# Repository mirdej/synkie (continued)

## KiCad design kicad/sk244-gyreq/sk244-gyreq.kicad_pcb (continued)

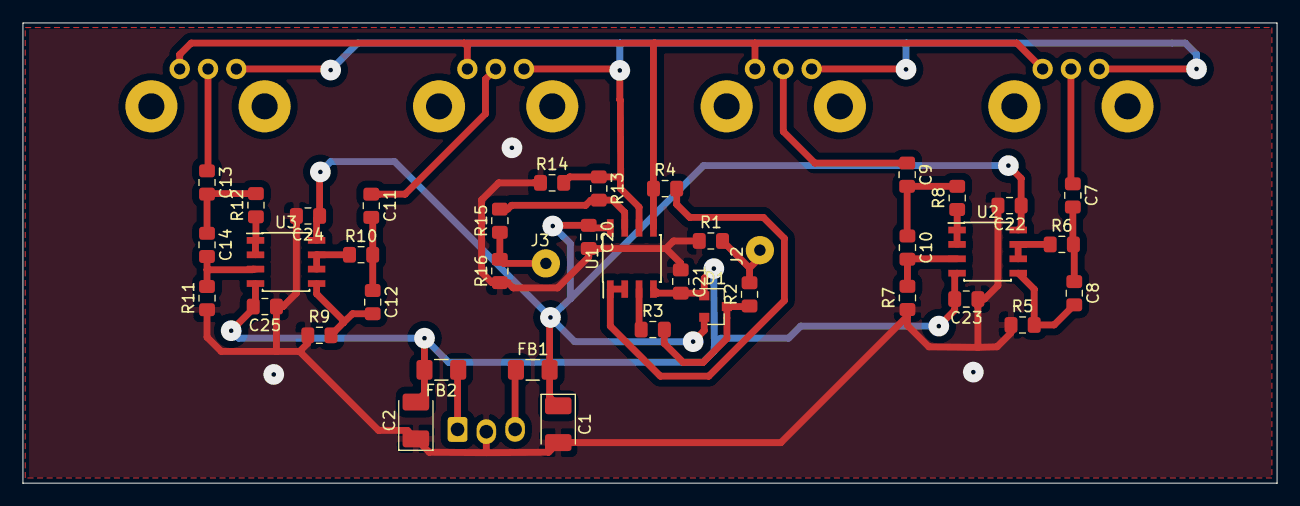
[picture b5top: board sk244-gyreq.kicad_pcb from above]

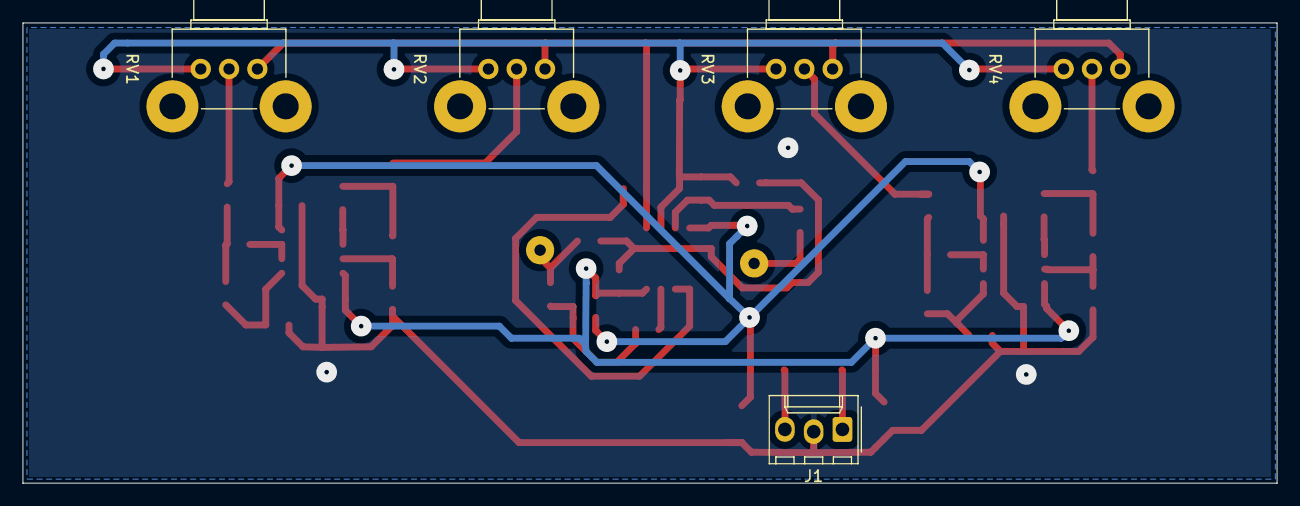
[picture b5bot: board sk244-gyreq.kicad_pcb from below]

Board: 2 copper layers, 110.7 x 40.6 mm, 45 parts (5 on the bottom side), 29 nets.

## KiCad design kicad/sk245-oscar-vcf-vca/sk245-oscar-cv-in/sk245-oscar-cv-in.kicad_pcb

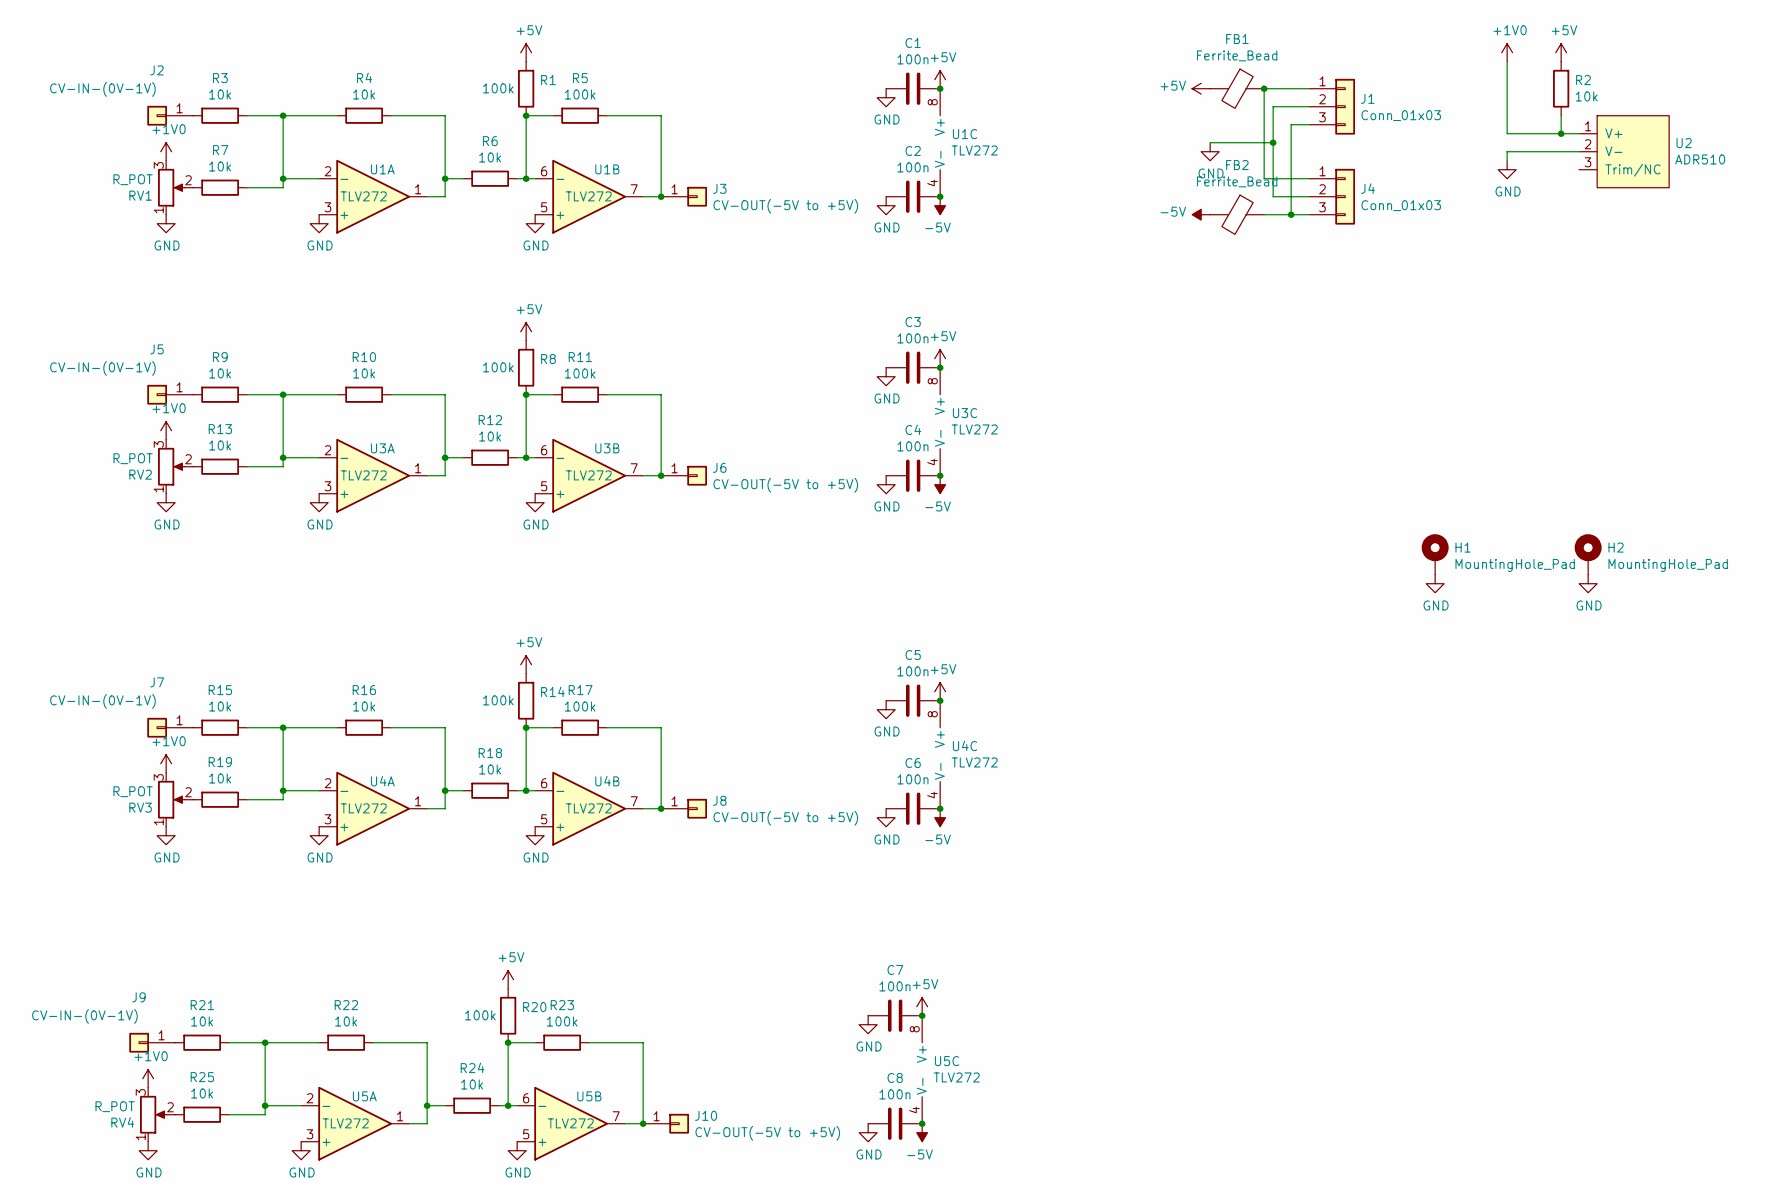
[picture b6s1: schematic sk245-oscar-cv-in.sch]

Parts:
C1, C2, C3, C4, C5, C6, C7, C8: 100n; C_0603_1608Metric_Pad1.05x0.95mm_HandSolder
FB1, FB2: Ferrite_Bead; L_0805_2012Metric_Pad1.15x1.40mm_HandSolder
H1, H2: MountingHole_Pad; MountingHole_3.2mm_M3_Pad
J1, J4: Conn_01x03; Molex_KK-254_AE-6410-03A_1x03_P2.54mm_Vertical
J2, J5, J7, J9: CV-IN-(0V-1V); Solderpad_1mm
J3, J6, J8, J10: CV-OUT(-5V to +5V); Solderpad_1mm
R1, R5, R8, R11, R14, R17, R20, R23: 100k; R_0805_2012Metric_Pad1.15x1.40mm_HandSolder
R2, R3, R4, R6, R7, R9, R10, R12, R13, R15, R16, R18, R19, R21, R22, R24, R25: 10k; R_0805_2012Metric_Pad1.15x1.40mm_HandSolder
RV1, RV2, RV3, RV4: R_POT; Potentiometer_Alps_RK09K_Single_Horizontal
U1, U3, U4, U5: TLV272; SOIC-8_3.9x4.9mm_P1.27mm
U2: ADR510; SOT-23

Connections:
+1V0: R2.1, RV1.3, RV2.3, RV3.3, RV4.3, U2.1 (V+)
+5V: C1.1, C3.1, C5.1, C7.1, FB1.2, R1.2, R2.2, R8.2, R14.2, R20.2, U1.8 (V+), U3.8 (V+), U4.8 (V+), U5.8 (V+)
-5V: C2.1, C4.1, C6.1, C8.1, FB2.2, U1.4 (V-), U3.4 (V-), U4.4 (V-), U5.4 (V-)
GND: C1.2, C2.2, C3.2, C4.2, C5.2, C6.2, C7.2, C8.2, H1.1, H2.1, J1.2, J4.2, RV1.1, RV2.1, RV3.1, RV4.1, U1.3 (+), U1.5 (+), U2.2 (V-), U3.3 (+), U3.5 (+), U4.3 (+), U4.5 (+), U5.3 (+), U5.5 (+)
unnamed: FB1.1, J1.1, J4.1
unnamed: FB2.1, J1.3, J4.3
unnamed: J2.1, R3.2
unnamed: J3.1, R5.1, U1.7
unnamed: J5.1, R9.2
unnamed: J6.1, R11.1, U3.7
unnamed: J7.1, R15.2
unnamed: J8.1, R17.1, U4.7
unnamed: J9.1, R21.2
unnamed: J10.1, R23.1, U5.7
unnamed: R1.1, R5.2, R6.1, U1.6 (-)
unnamed: R3.1, R4.2, R7.1, U1.2 (-)
unnamed: R4.1, R6.2, U1.1
unnamed: R7.2, RV1.2
unnamed: R10.1, R12.2, U3.1
unnamed: R9.1, R10.2, R13.1, U3.2 (-)
unnamed: R8.1, R11.2, R12.1, U3.6 (-)
unnamed: R13.2, RV2.2
unnamed: R14.1, R17.2, R18.1, U4.6 (-)
unnamed: R15.1, R16.2, R19.1, U4.2 (-)
unnamed: R16.1, R18.2, U4.1
unnamed: R19.2, RV3.2
unnamed: R20.1, R23.2, R24.1, U5.6 (-)
unnamed: R21.1, R22.2, R25.1, U5.2 (-)
unnamed: R22.1, R24.2, U5.1
unnamed: R25.2, RV4.2

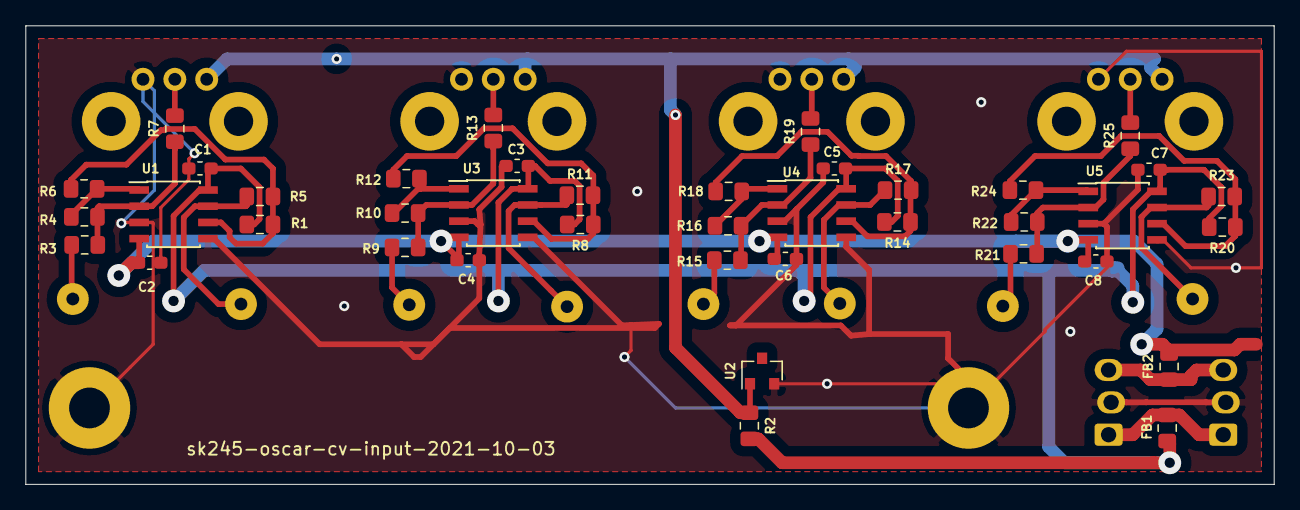
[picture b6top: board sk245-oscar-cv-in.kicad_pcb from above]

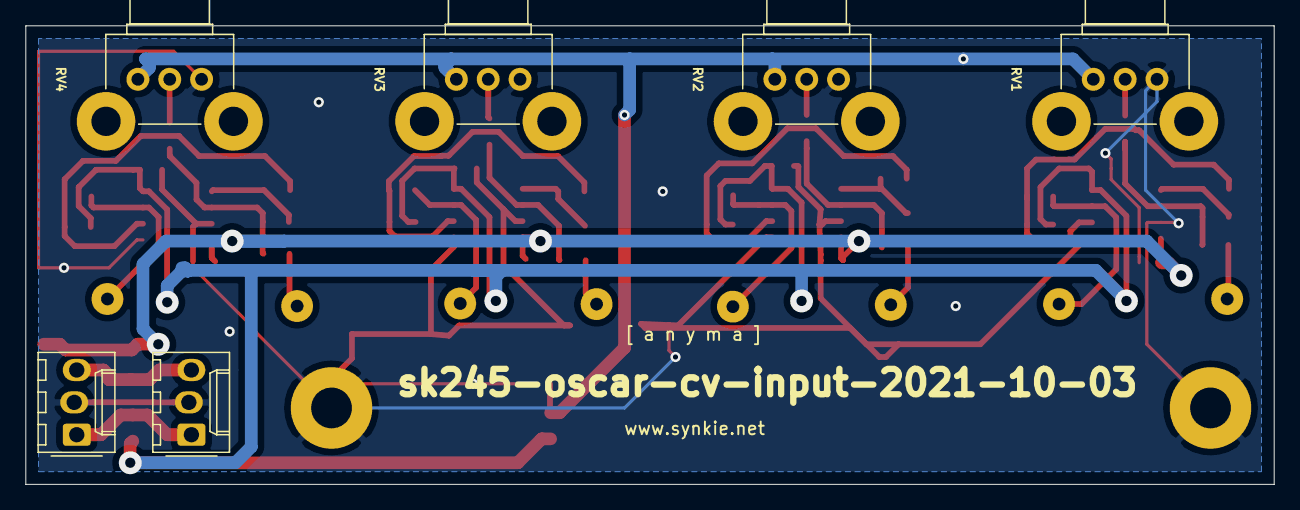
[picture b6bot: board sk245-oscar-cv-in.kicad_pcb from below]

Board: 2 copper layers, 98.0 x 36.0 mm, 56 parts (6 on the bottom side), 30 nets.

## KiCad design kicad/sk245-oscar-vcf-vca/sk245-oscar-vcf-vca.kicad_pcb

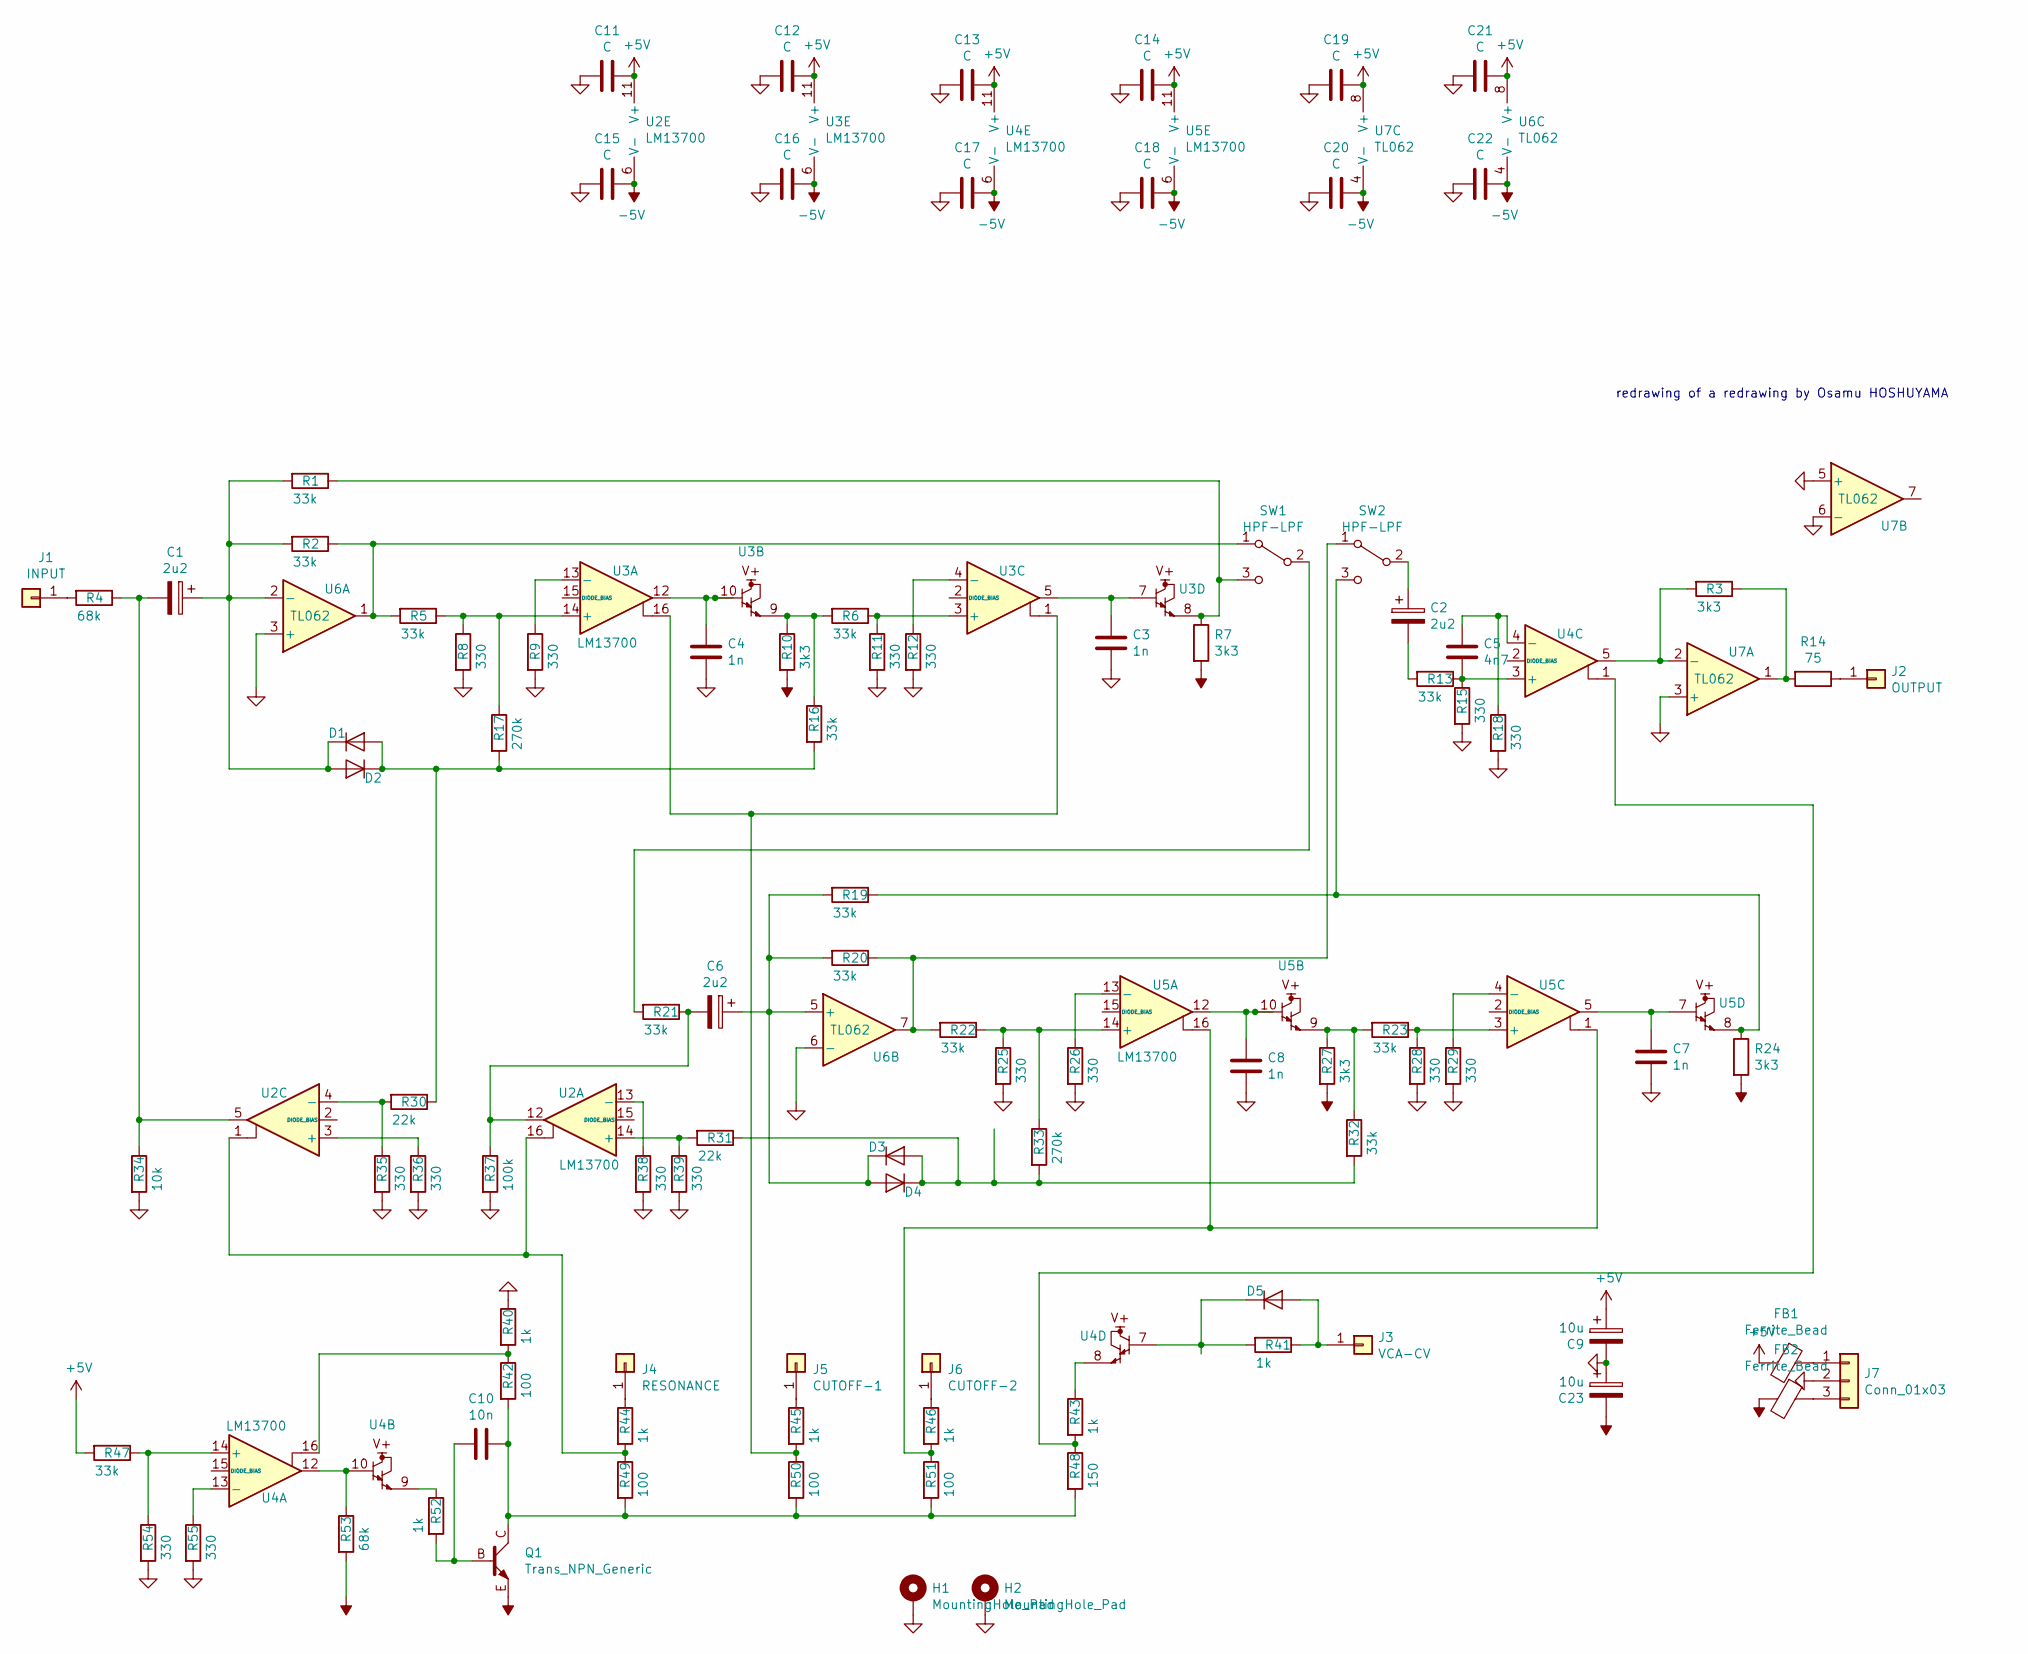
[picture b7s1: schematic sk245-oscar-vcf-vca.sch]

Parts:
C1: 2u2; C_1206_3216Metric_Pad1.42x1.75mm_HandSolder
C2, C6: 2u2; R_1206_3216Metric_Pad1.42x1.75mm_HandSolder
C3, C4, C7, C8: 1n; R_1206_3216Metric_Pad1.42x1.75mm_HandSolder
C5: 4n7; R_1206_3216Metric_Pad1.42x1.75mm_HandSolder
C9, C23: 10u; R_1206_3216Metric_Pad1.42x1.75mm_HandSolder
C10: 10n; C_1206_3216Metric_Pad1.42x1.75mm_HandSolder
C11, C12, C13, C14, C15, C16, C17, C18, C19, C20, C21, C22: C; C_0603_1608Metric_Pad1.05x0.95mm_HandSolder
D1, D2, D3, D4, D5: D; D_MiniMELF_Handsoldering
FB1, FB2: Ferrite_Bead; L_1206_3216Metric_Pad1.42x1.75mm_HandSolder
H1, H2: MountingHole_Pad; MountingHole_3.2mm_M3_ISO7380_Pad
J1: INPUT; Solderpad_1mm
J2: OUTPUT; Solderpad_1mm
J3: VCA-CV; Solderpad_1mm
J4: RESONANCE; Solderpad_1mm
J5: CUTOFF-1; Solderpad_1mm
J6: CUTOFF-2; Solderpad_1mm
J7: Conn_01x03; Molex_KK-254_AE-6410-03A_1x03_P2.54mm_Vertical
Q1: Trans_NPN_Generic; SOT-23_BEC
R1, R2, R5, R6, R13, R16, R19, R20, R21, R22, R23, R32, R47: 33k; R_0805_2012Metric_Pad1.15x1.40mm_HandSolder
R3, R7, R10, R24, R27: 3k3; R_0805_2012Metric_Pad1.15x1.40mm_HandSolder
R4, R53: 68k; R_0805_2012Metric_Pad1.15x1.40mm_HandSolder
R8, R9, R11, R12, R15, R18, R25, R26, R28, R29, R35, R36, R38, R39, R54, R55: 330; R_0805_2012Metric_Pad1.15x1.40mm_HandSolder
R14: 75; R_0805_2012Metric_Pad1.15x1.40mm_HandSolder
R17, R33: 270k; R_0805_2012Metric_Pad1.15x1.40mm_HandSolder
R30, R31: 22k; R_0805_2012Metric_Pad1.15x1.40mm_HandSolder
R34: 10k; R_0805_2012Metric_Pad1.15x1.40mm_HandSolder
R37: 100k; R_0805_2012Metric_Pad1.15x1.40mm_HandSolder
R40, R41, R43, R44, R45, R46, R52: 1k; R_0805_2012Metric_Pad1.15x1.40mm_HandSolder
R42, R49, R50, R51: 100; R_0805_2012Metric_Pad1.15x1.40mm_HandSolder
R48: 150; R_0805_2012Metric_Pad1.15x1.40mm_HandSolder
SW1, SW2: HPF-LPF; PinHeader_1x03_P2.54mm_Vertical
U2, U3, U4, U5: LM13700; SOIC-16_3.9x9.9mm_P1.27mm
U6, U7: TL062; SOIC-8_3.9x4.9mm_P1.27mm

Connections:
+5V: C9.1, C11.1, C12.1, C13.1, C14.1, C19.1, C21.1, FB1.2, R47.2, U2.11 (V+), U3.11 (V+), U4.11 (V+), U5.11 (V+), U6.8 (V+), U7.8 (V+)
-5V: C15.1, C16.1, C17.1, C18.1, C20.1, C22.1, C23.2, FB2.2, Q1.E, R7.2, R10.2, R24.2, R27.2, R53.2, U2.6 (V-), U3.6 (V-), U4.6 (V-), U5.6 (V-), U6.4 (V-), U7.4 (V-)
GND: C3.2, C4.2, C7.2, C8.2, C9.2, C11.2, C12.2, C13.2, C14.2, C15.2, C16.2, C17.2, C18.2, C19.2, C20.2, C21.2, C22.2, C23.1, H1.1, H2.1, J7.2, R8.2, R9.2, R11.2, R12.2, R15.2, R18.2, R25.2, R26.2, R28.2, R29.2, R34.2, R35.2, R36.2, R37.2, R38.2, R39.2, R40.1, R54.2, R55.2, U6.3 (+), U6.6 (-), U7.3 (+), U7.5 (+), U7.6 (-)
unnamed: C1.1, D1.1 (K), D2.2 (A), R1.2, R2.2, U6.2 (-)
unnamed: C1.2, R4.1, R34.1, U2.5
unnamed: C2.1, SW2.2 (B)
unnamed: C2.2, R13.2
unnamed: C3.1, U3.5, U3.7
unnamed: C4.1, U3.10, U3.12
unnamed: C5.1, R18.1, U4.4 (-)
unnamed: C5.2, R13.1, R15.1, U4.3 (+)
unnamed: C6.1, D3.1 (K), D4.2 (A), R19.2, R20.2, U6.5 (+)
unnamed: C6.2, R21.1, R37.1, U2.12
unnamed: C7.1, U5.5, U5.7
unnamed: C8.1, U5.10, U5.12
unnamed: C10.1, Q1.C, R42.2, R48.2, R49.2, R50.2, R51.2
unnamed: C10.2, Q1.B, R52.2
unnamed: D1.2 (A), D2.1 (K), R16.2, R17.2, R30.1
unnamed: D3.2 (A), D4.1 (K), R31.1, R32.2, R33.2
unnamed: D5.1 (K), R41.2, U4.7
unnamed: D5.2 (A), J3.1, R41.1
unnamed: FB1.1, J7.1
unnamed: FB2.1, J7.3
unnamed: J1.1, R4.2
unnamed: J2.1, R14.1
unnamed: J4.1, R44.1
unnamed: J5.1, R45.1
unnamed: J6.1, R46.1
unnamed: R1.1, R7.1, SW1.3 (C), U3.8
unnamed: R2.1, R5.2, SW1.1 (A), U6.1
unnamed: R3.2, U4.5, U7.2 (-)
unnamed: R9.1, U3.13 (-)
unnamed: R6.2, R10.1, R16.1, U3.9
unnamed: R6.1, R11.1, U3.3 (+)
unnamed: R12.1, U3.4 (-)
unnamed: R3.1, R14.2, U7.1
unnamed: R5.1, R8.1, R17.1, U3.14 (+)
unnamed: R19.1, R24.1, SW2.3 (C), U5.8
unnamed: R20.1, R22.2, SW2.1 (A), U6.7
unnamed: R21.2, SW1.2 (B)
unnamed: R22.1, R25.1, R33.1, U5.14 (+)
unnamed: R23.1, R28.1, U5.3 (+)
unnamed: R23.2, R27.1, R32.1, U5.9
unnamed: R26.1, U5.13 (-)
unnamed: R29.1, U5.4 (-)
unnamed: R30.2, R35.1, U2.4 (-)
unnamed: R31.2, R39.1, U2.14 (+)
unnamed: R36.1, U2.3 (+)
unnamed: R38.1, U2.13 (-)
unnamed: R40.2, R42.1, U4.16
unnamed: R43.1, U4.8
unnamed: R43.2, R48.1, U4.1
unnamed: R44.2, R49.1, U2.1, U2.16
unnamed: R45.2, R50.1, U3.1, U3.16
unnamed: R46.2, R51.1, U5.1, U5.16
unnamed: R47.1, R54.1, U4.14 (+)
unnamed: R52.1, U4.9
unnamed: R53.1, U4.10, U4.12
unnamed: R55.1, U4.13 (-)

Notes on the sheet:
redrawing of a redrawing by Osamu HOSHUYAMA

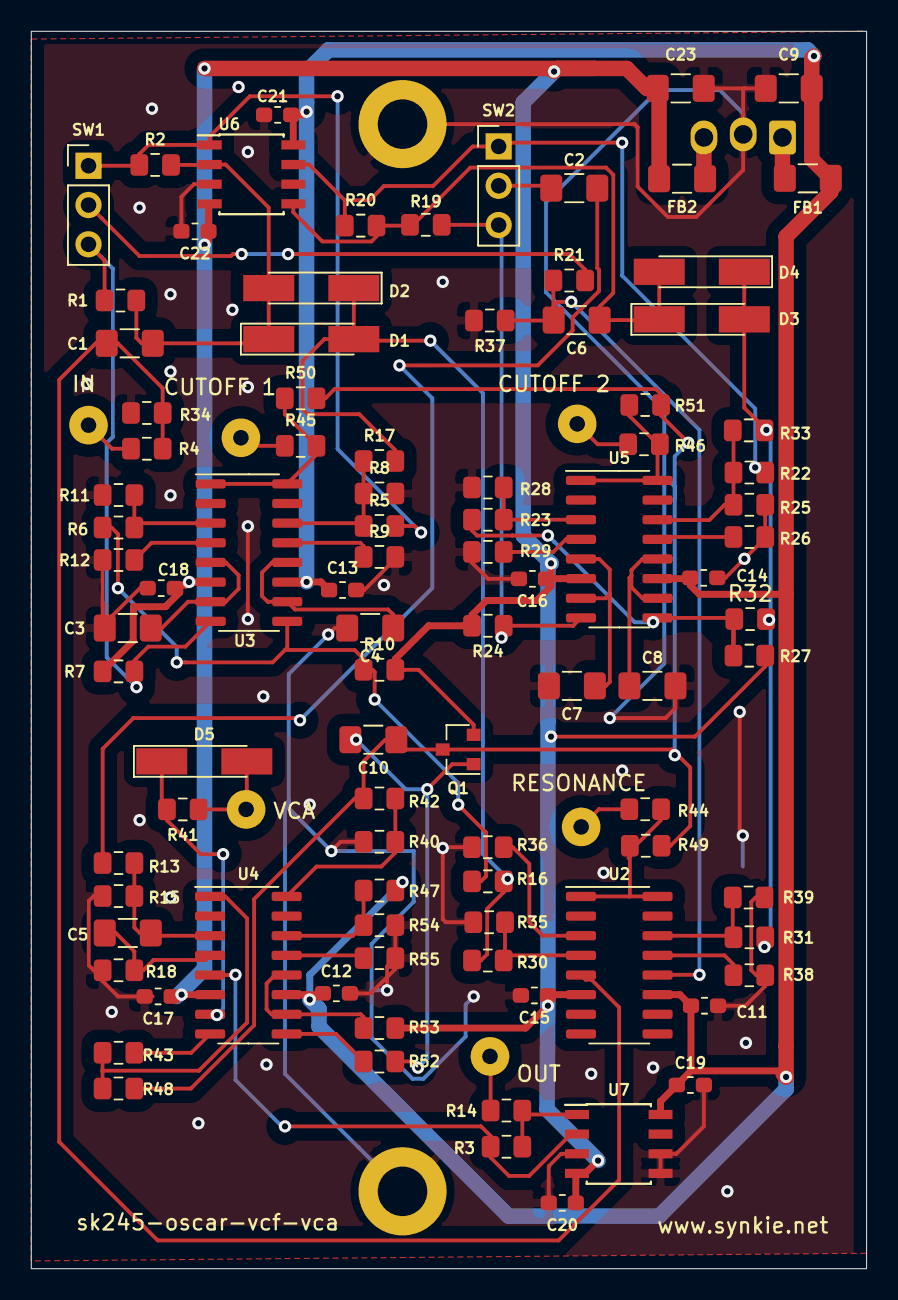
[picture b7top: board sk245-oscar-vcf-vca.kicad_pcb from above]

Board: 2 copper layers, 54.0 x 80.0 mm, 103 parts (1 on the bottom side), 59 nets.

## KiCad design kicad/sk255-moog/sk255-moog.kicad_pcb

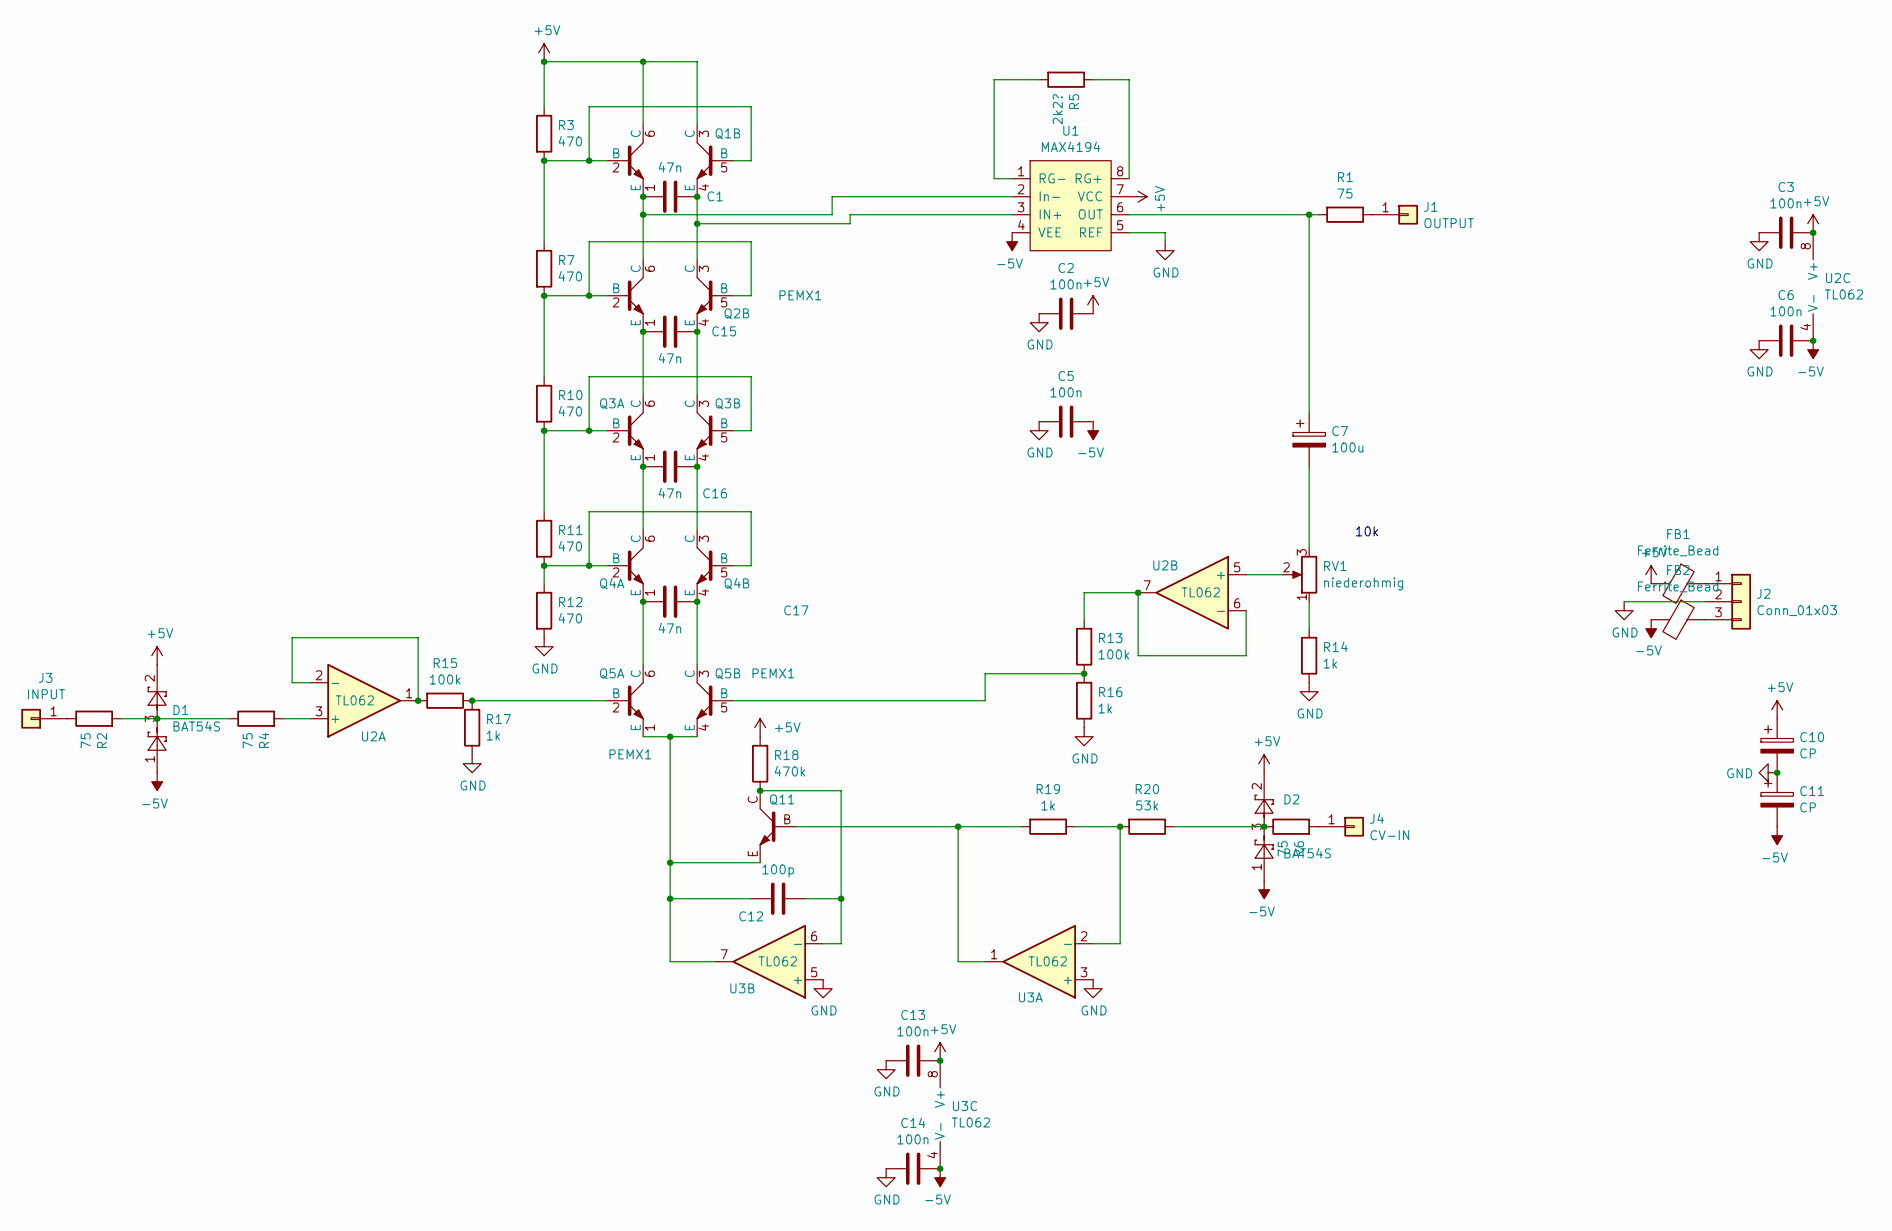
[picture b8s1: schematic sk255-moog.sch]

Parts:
C1, C15, C16, C17: 47n; C_0805_2012Metric_Pad1.15x1.40mm_HandSolder
C2, C3, C5, C6, C13, C14: 100n; C_0603_1608Metric_Pad1.05x0.95mm_HandSolder
C7: 100u; CP_EIA-3528-21_Kemet-B_Pad1.50x2.35mm_HandSolder
C10, C11: CP; C_1206_3216Metric_Pad1.42x1.75mm_HandSolder
C12: 100p; C_0805_2012Metric_Pad1.15x1.40mm_HandSolder
D1, D2: BAT54S; SOT-23
FB1, FB2: Ferrite_Bead; L_0805_2012Metric_Pad1.15x1.40mm_HandSolder
J1: OUTPUT; Solderpad_1mm
J2: Conn_01x03; Molex_KK-254_AE-6410-03A_1x03_P2.54mm_Vertical
J3: INPUT; Solderpad_1mm
J4: CV-IN; Solderpad_1mm
Q1, Q2, Q3, Q4, Q5: PEMX1; SOT-666
Q11: Trans_NPN_Generic; SOT-23_BEC
R1, R2, R4, R6: 75; R_0805_2012Metric_Pad1.15x1.40mm_HandSolder
R3, R7, R10, R11, R12: 470; R_0805_2012Metric_Pad1.15x1.40mm_HandSolder
R5: 2k2?; R_0805_2012Metric_Pad1.15x1.40mm_HandSolder
R13, R15: 100k; R_0805_2012Metric_Pad1.15x1.40mm_HandSolder
R14, R16, R17, R19: 1k; R_0805_2012Metric_Pad1.15x1.40mm_HandSolder
R18: 470k; R_0805_2012Metric_Pad1.15x1.40mm_HandSolder
R20: 53k; R_0805_2012Metric_Pad1.15x1.40mm_HandSolder
RV1: niederohmig; Potentiometer_Alps_RK09K_Single_Horizontal
U1: MAX4194; SOIC-8_3.9x4.9mm_P1.27mm
U2, U3: TL062; SOIC-8_3.9x4.9mm_P1.27mm

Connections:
+5V: C2.1, C3.1, C10.1, C13.1, D1.2, D2.2, FB1.2, Q1.3 (C), Q1.6 (C), R3.1, R18.2, U1.7 (VCC), U2.8 (V+), U3.8 (V+)
-5V: C5.1, C6.1, C11.2, C14.1, D1.1, D2.1, FB2.2, U1.4 (VEE), U2.4 (V-), U3.4 (V-)
GND: C2.2, C3.2, C5.2, C6.2, C10.2, C11.1, C13.2, C14.2, J2.2, R12.2, R14.1, R16.1, R17.1, U1.5 (REF), U3.3 (+), U3.5 (+)
unnamed: C1.1, Q1.4 (E), Q2.3 (C), U1.3 (IN+)
unnamed: C1.2, Q1.1 (E), Q2.6 (C), U1.2 (In-)
unnamed: C7.1, R1.2, U1.6 (OUT)
unnamed: C7.2, RV1.3
unnamed: C12.1, Q11.C, R18.1, U3.6 (-)
unnamed: C12.2, Q5.1 (E), Q5.4 (E), Q11.E, U3.7
unnamed: C15.1, Q2.4 (E), Q3.3 (C)
unnamed: C15.2, Q2.1 (E), Q3.6 (C)
unnamed: C16.1, Q3.4 (E), Q4.3 (C)
unnamed: C16.2, Q3.1 (E), Q4.6 (C)
unnamed: C17.1, Q4.4 (E), Q5.3 (C)
unnamed: C17.2, Q4.1 (E), Q5.6 (C)
unnamed: D1.3, R2.2, R4.1
unnamed: D2.3, R6.1, R20.1
unnamed: FB1.1, J2.1
unnamed: FB2.1, J2.3
unnamed: J1.1, R1.1
unnamed: J3.1, R2.1
unnamed: J4.1, R6.2
unnamed: Q1.2 (B), Q1.5 (B), R3.2, R7.1
unnamed: Q2.2 (B), Q2.5 (B), R7.2, R10.1
unnamed: Q3.2 (B), Q3.5 (B), R10.2, R11.1
unnamed: Q4.2 (B), Q4.5 (B), R11.2, R12.1
unnamed: Q5.2 (B), R15.1, R17.2
unnamed: Q5.5 (B), R13.1, R16.2
unnamed: Q11.B, R19.2, U3.1
unnamed: R4.2, U2.3 (+)
unnamed: R5.1, U1.8 (RG+)
unnamed: R5.2, U1.1 (RG-)
unnamed: R13.2, U2.6 (-), U2.7
unnamed: R14.2, RV1.1
unnamed: R15.2, U2.1, U2.2 (-)
unnamed: R19.1, R20.2, U3.2 (-)
unnamed: RV1.2, U2.5 (+)

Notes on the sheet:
10k

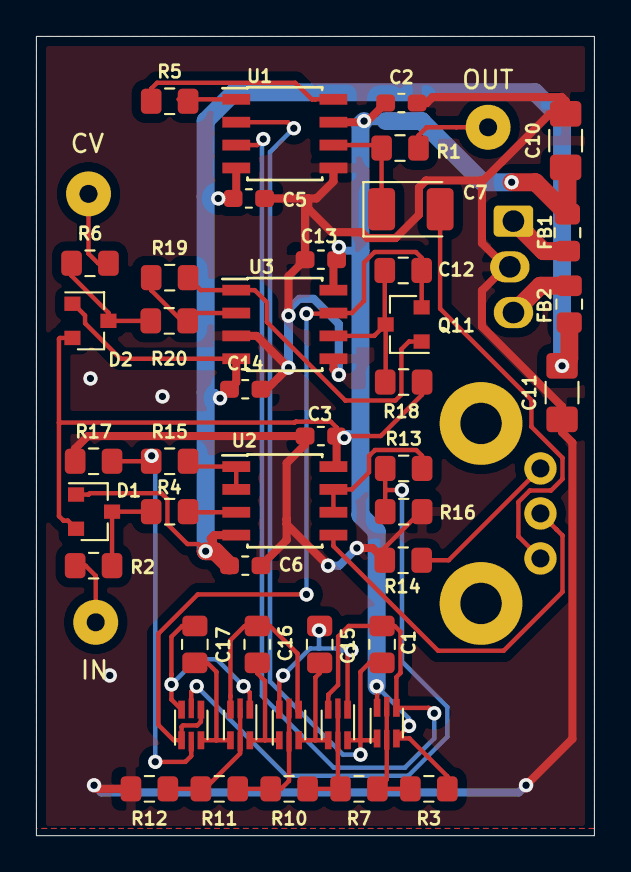
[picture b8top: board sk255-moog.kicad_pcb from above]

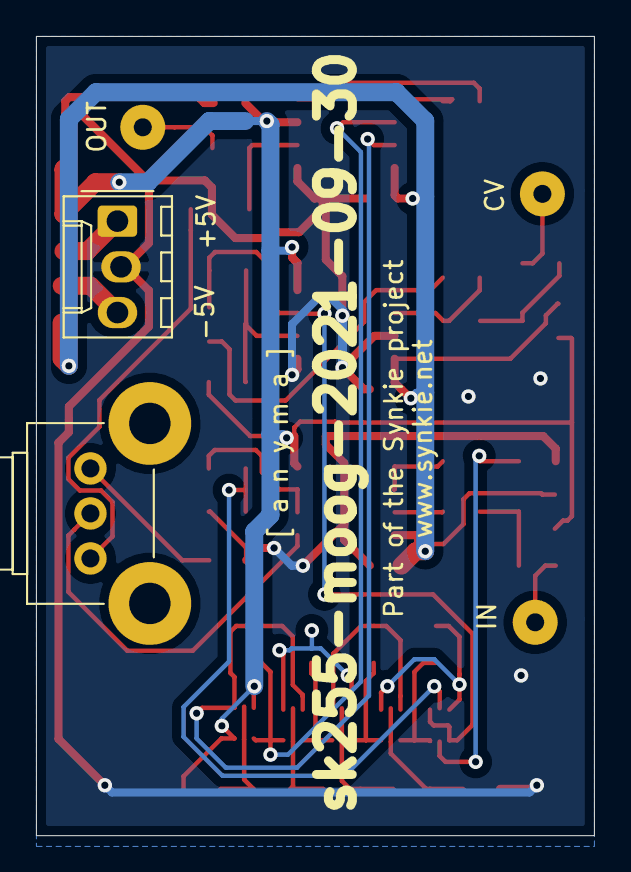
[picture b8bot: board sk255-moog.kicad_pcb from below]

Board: 2 copper layers, 31.0 x 44.4 mm, 50 parts (2 on the bottom side), 37 nets.
